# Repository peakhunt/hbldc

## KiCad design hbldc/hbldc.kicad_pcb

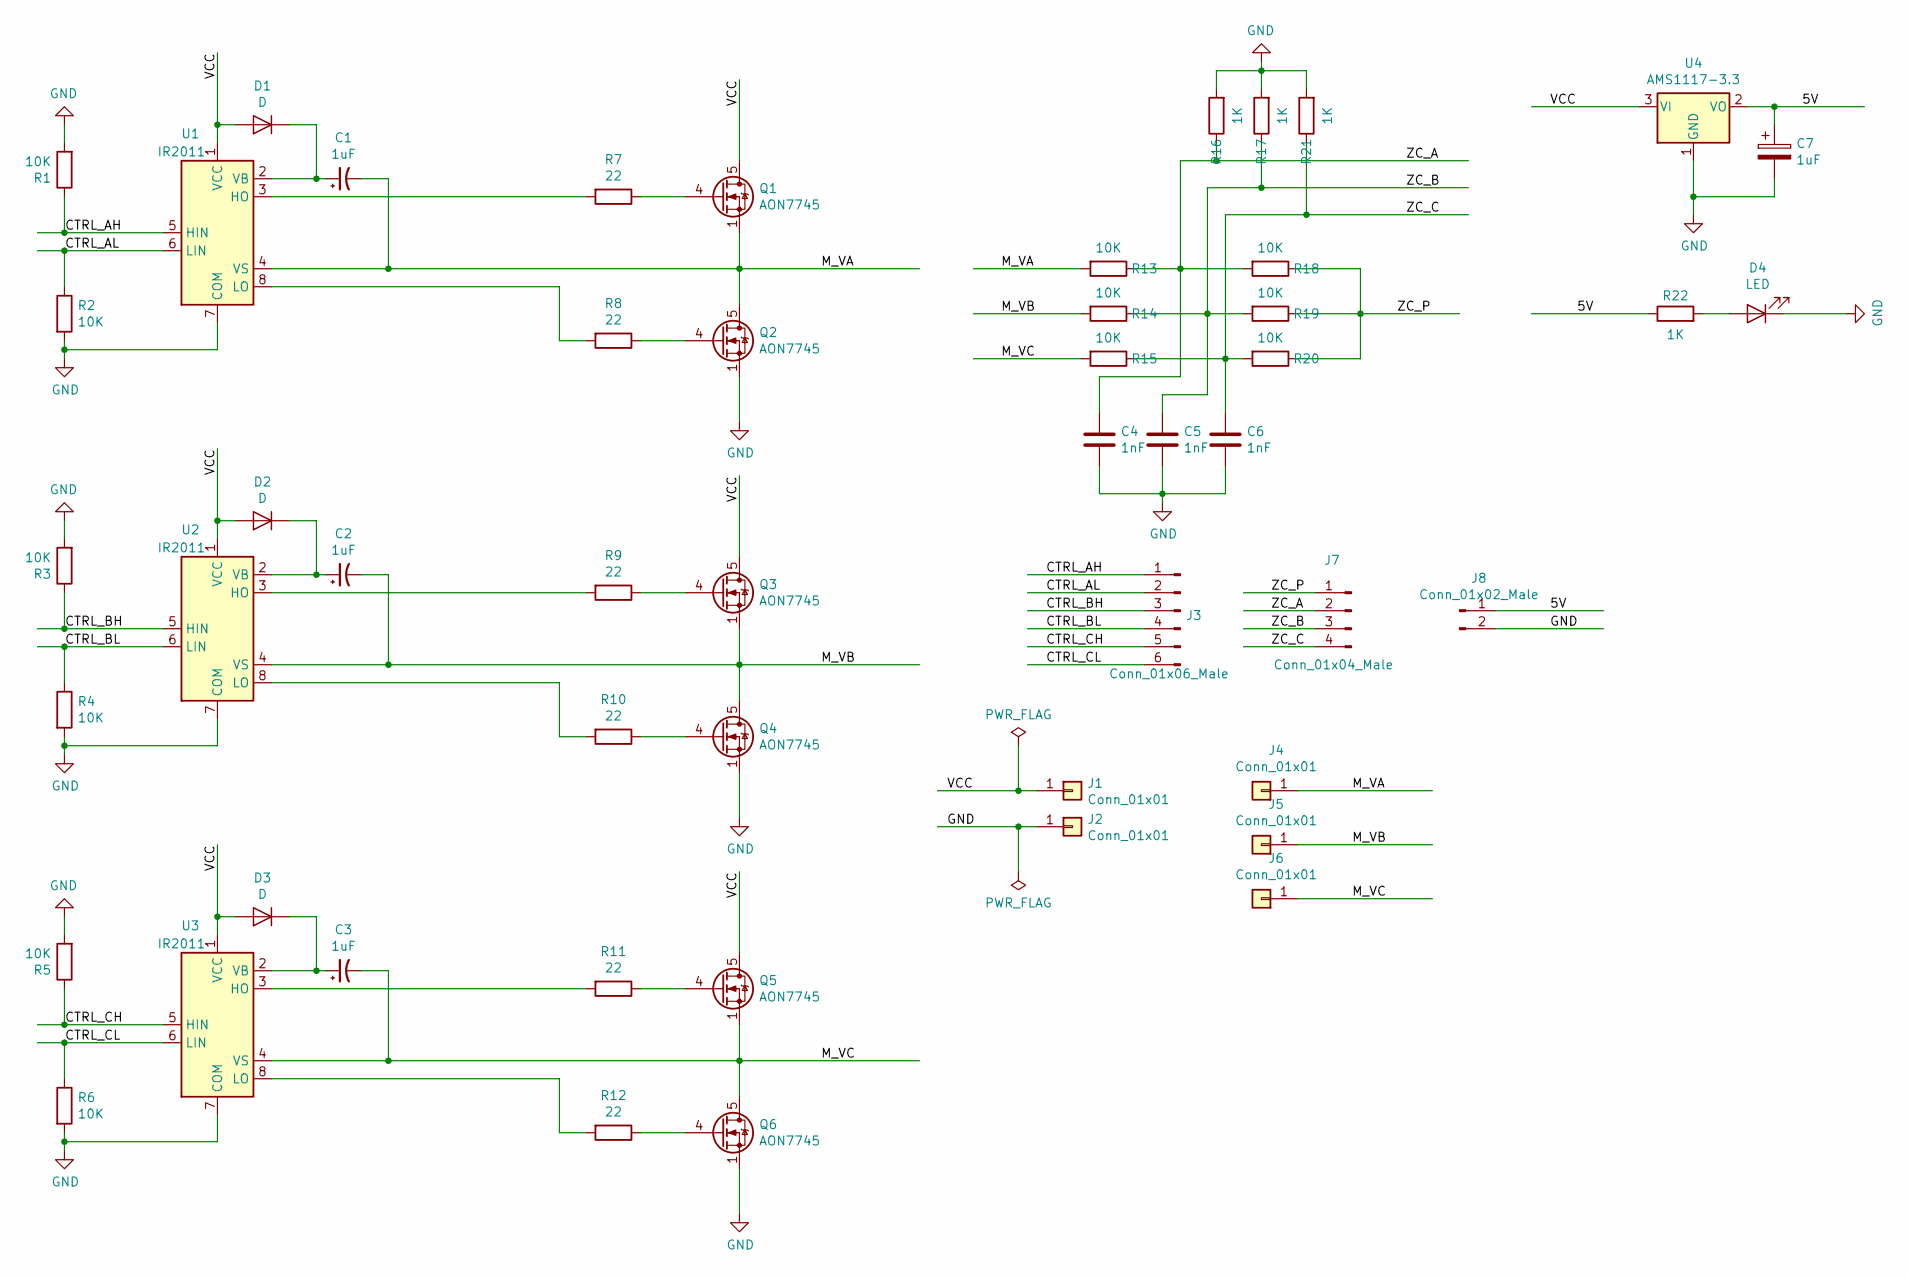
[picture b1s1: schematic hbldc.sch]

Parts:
C1, C2, C3, C7: 1uF; CP_Tantalum_Case-A_EIA-3216-18_Hand
C4, C5, C6: 1nF; C_0603
D1, D2, D3: D; D_SOD-323
D4: LED; LED_0603
J1, J2: Conn_01x01; SolderWirePad_single_1-5mmDrill
J3: Conn_01x06_Male; Pin_Header_Straight_1x06_Pitch2.54mm
J4, J5, J6: Conn_01x01; SolderWirePad_single_0-8mmDrill
J7: Conn_01x04_Male; Pin_Header_Straight_1x04_Pitch2.54mm
J8: Conn_01x02_Male; Pin_Header_Straight_1x02_Pitch2.54mm
Q1, Q2, Q3, Q4, Q5, Q6: AON7745; TDSON-8-1
R1, R2, R3, R4, R5, R6, R13, R14, R15, R18, R19, R20: 10K; R_0603
R7, R8, R9, R10, R11, R12: 22; R_0603
R16, R17, R21, R22: 1K; R_0603
U1, U2, U3: IR2011; SOIC-8_3.9x4.9mm_Pitch1.27mm
U4: AMS1117-3.3; SOT-223

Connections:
/5V: C7.1, J8.1, R22.1, U4.2 (VO)
/CTRL_AH: J3.1, R1.1, U1.5 (HIN)
/CTRL_AL: J3.2, R2.1, U1.6 (LIN)
/CTRL_BH: J3.3, R3.1, U2.5 (HIN)
/CTRL_BL: J3.4, R4.1, U2.6 (LIN)
/CTRL_CH: J3.5, R5.1, U3.5 (HIN)
/CTRL_CL: J3.6, R6.1, U3.6 (LIN)
/M_VA: C1.2, J4.1, Q1.1 (S), Q1.2 (S), Q1.3 (S), Q2.5 (D), R13.2, U1.4 (VS)
/M_VB: C2.2, J5.1, Q3.1 (S), Q3.2 (S), Q3.3 (S), Q4.5 (D), R14.2, U2.4 (VS)
/M_VC: C3.2, J6.1, Q5.1 (S), Q5.2 (S), Q5.3 (S), Q6.5 (D), R15.2, U3.4 (VS)
/VCC: D1.2 (A), D2.2 (A), D3.2 (A), J1.1, Q1.5 (D), Q3.5 (D), Q5.5 (D), U1.1 (VCC), U2.1 (VCC), U3.1 (VCC), U4.3 (VI)
/ZC_A: C4.2, J7.2, R13.1, R16.1, R18.2
/ZC_B: C5.2, J7.3, R14.1, R17.1, R19.2
/ZC_C: C6.2, J7.4, R15.1, R20.2, R21.1
/ZC_P: J7.1, R18.1, R19.1, R20.1
GND: C4.1, C5.1, C6.1, C7.2, D4.1 (K), J2.1, J8.2, Q2.1 (S), Q2.2 (S), Q2.3 (S), Q4.1 (S), Q4.2 (S), Q4.3 (S), Q6.1 (S), Q6.2 (S), Q6.3 (S), R1.2, R2.2, R3.2, R4.2, R5.2, R6.2, R16.2, R17.2, R21.2, U1.7 (COM), U2.7 (COM), U3.7 (COM), U4.1 (GND)
unnamed: C1.1, D1.1 (K), U1.2 (VB)
unnamed: C2.1, D2.1 (K), U2.2 (VB)
unnamed: C3.1, D3.1 (K), U3.2 (VB)
unnamed: D4.2 (A), R22.2
unnamed: Q1.4 (G), R7.1
unnamed: Q2.4 (G), R8.1
unnamed: Q3.4 (G), R9.1
unnamed: Q4.4 (G), R10.1
unnamed: Q5.4 (G), R11.1
unnamed: Q6.4 (G), R12.1
unnamed: R7.2, U1.3 (HO)
unnamed: R8.2, U1.8 (LO)
unnamed: R9.2, U2.3 (HO)
unnamed: R10.2, U2.8 (LO)
unnamed: R11.2, U3.3 (HO)
unnamed: R12.2, U3.8 (LO)

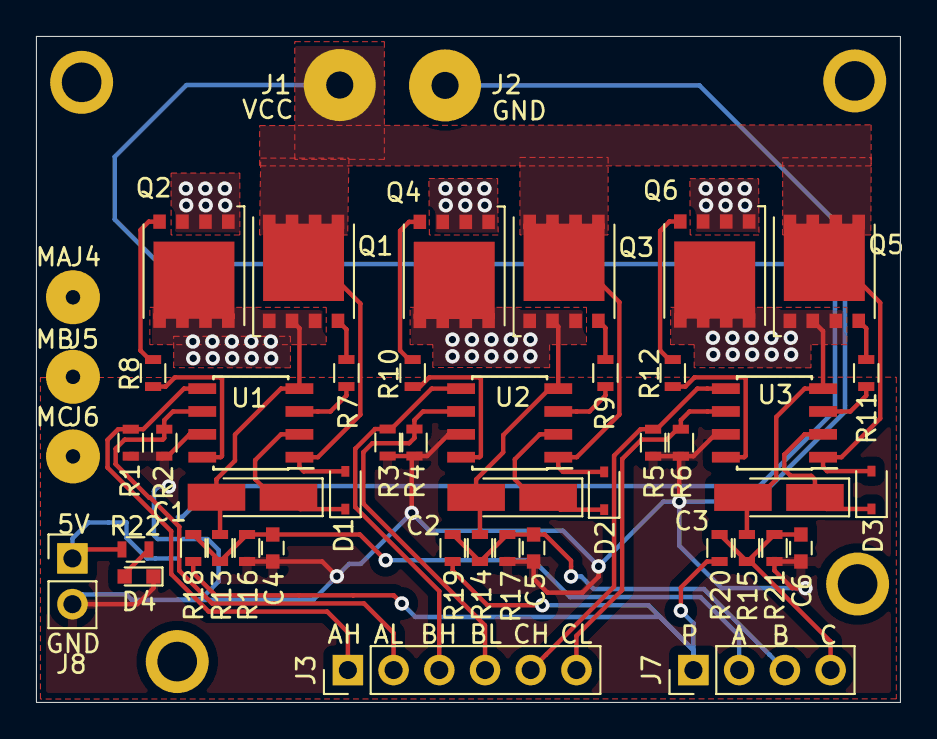
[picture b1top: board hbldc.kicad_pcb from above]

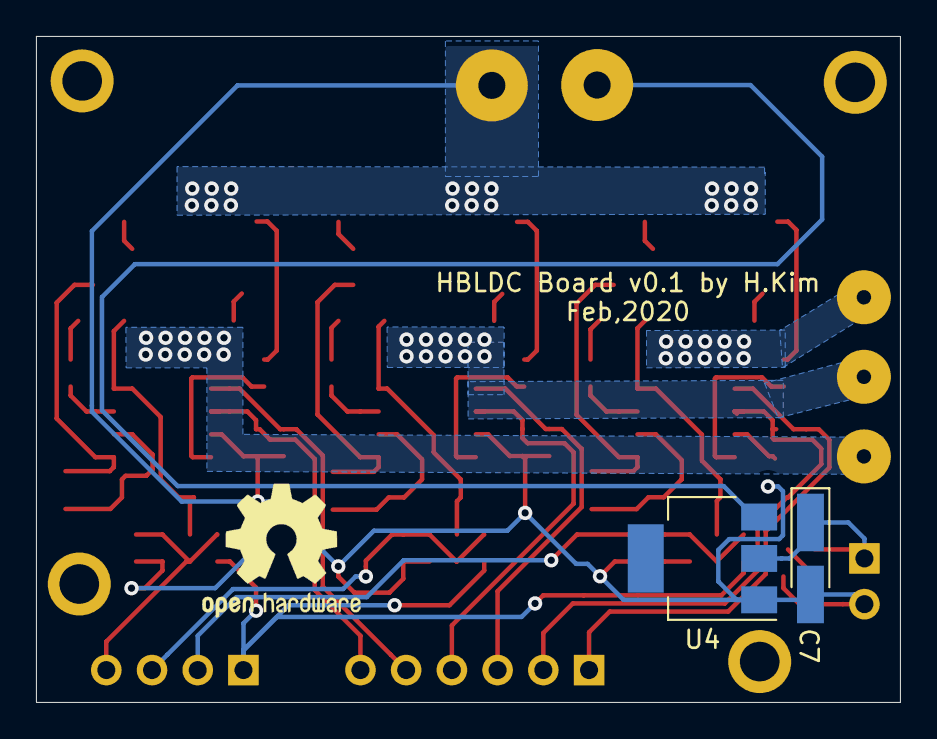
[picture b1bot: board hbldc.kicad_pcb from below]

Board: 2 copper layers, 48.0 x 37.0 mm, 51 parts (2 on the bottom side), 32 nets.

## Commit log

2020-02-27 initial import
2020-02-27 removed unnecessary digikey libraries
